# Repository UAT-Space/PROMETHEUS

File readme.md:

# PROMETHEUS

###### If you need to contact me do it [here](mailto:AndrewRLong02@gmail.com). <br> My advice is to entirely remake the build system

### Buildroot
This is the build system for linux that runs on a raspberry pi zero w.  
The python scripts that get data from the hardware are in ./overlay/usr/local/bin/ins.py.  
The script that starts data collection and video recording is at ./overlay/etc/init.d/S91set, the functions of the script has been disabled as data and video were manualy started.  
<br>
The external temperature probe and gps were removed from the scripts because of time constraints.

***DO NOT RE-INIT, YOU WILL LOSE THE KERNEL AND SYSTEM CONFIG. IF THIS HAPPENS YOU WILL HAVE TO REDO ALMOST EVERYTHING.***

### PCBS
The folder "Flight_Comp" contains the custom hat for the raspberry pi zero w.

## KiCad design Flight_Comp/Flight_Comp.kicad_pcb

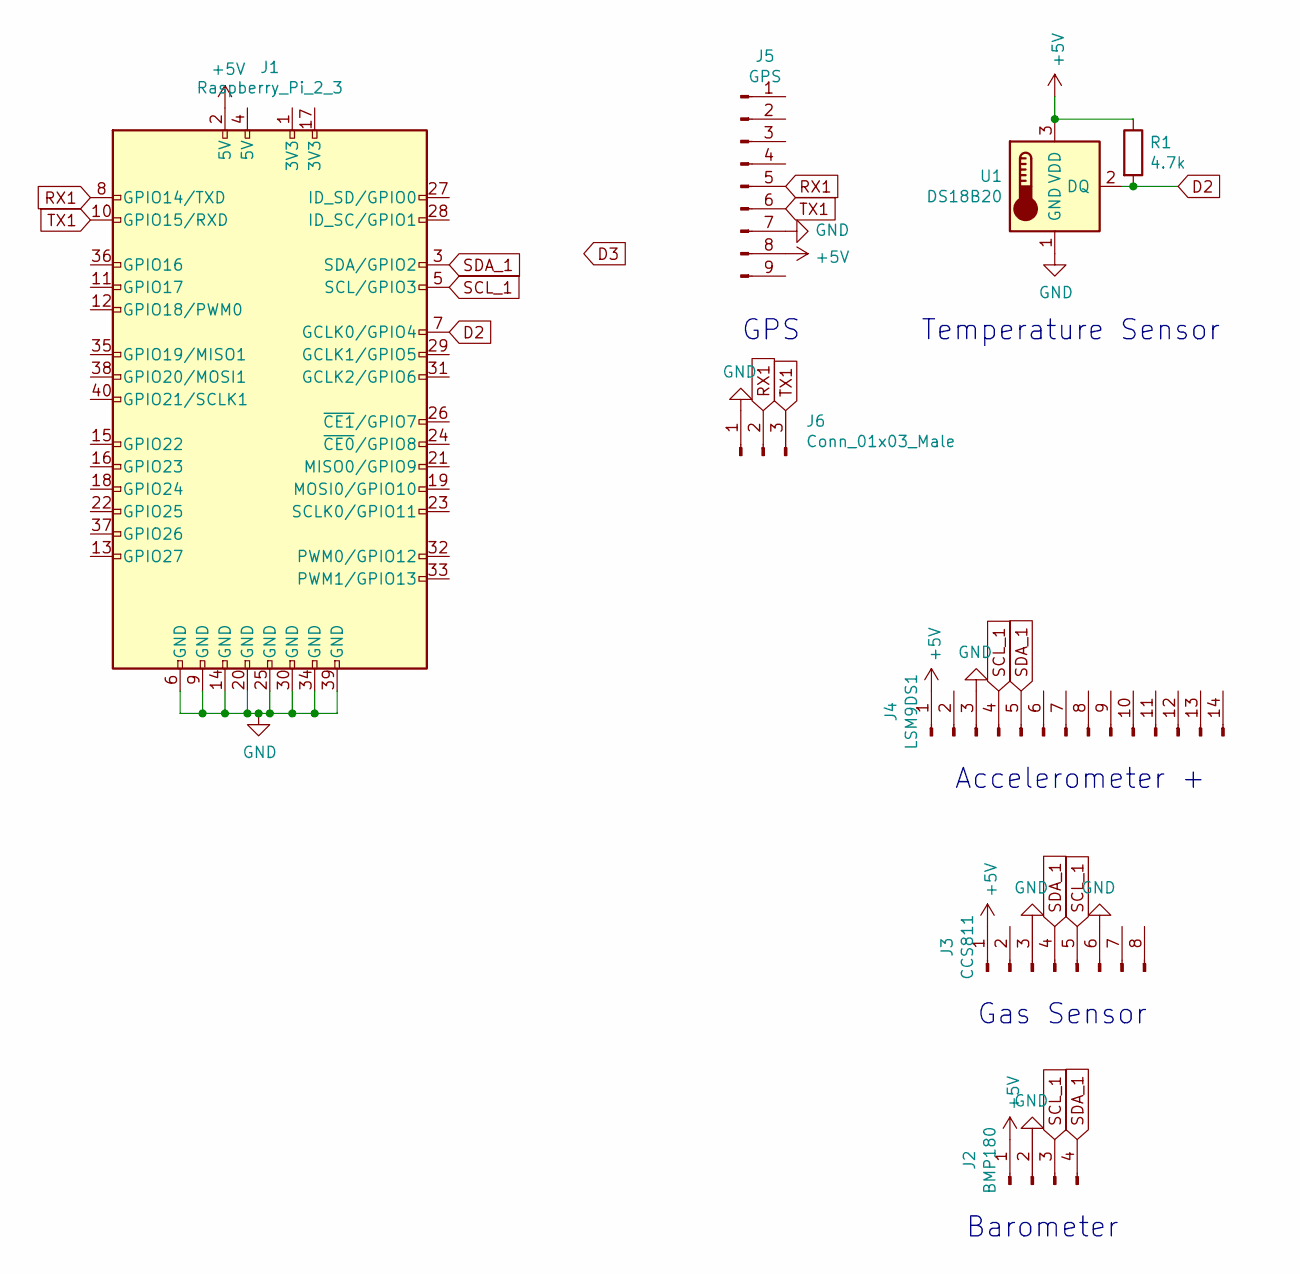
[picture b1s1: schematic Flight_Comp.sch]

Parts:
J1: Raspberry_Pi_2_3; pi zero w
J2: BMP180; JBtec BMP180
J3: CCS811
J4: LSM9DS1
J5: GPS; uGPS Bv3
J6: Conn_01x03_Male; PinSocket_1x03_P2.54mm_Vertical
R1: 4.7k; R_0805_2012Metric
U1: DS18B20; PinSocket_1x03_P2.54mm_Vertical

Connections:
+5V: J1.2 (5V), J2.1, J3.1, J4.1, J5.8, R1.1, U1.3 (VDD)
D2: J1.7 (GCLK0/GPIO4), R1.2, U1.2 (DQ)
GND: J1.6 (GND), J1.9 (GND), J1.14 (GND), J1.20 (GND), J1.25 (GND), J1.30 (GND), J1.34 (GND), J1.39 (GND), J2.2, J3.3, J3.6, J4.3, J5.7, J6.1, U1.1 (GND)
RX1: J1.8 (GPIO14/TXD), J5.5, J6.2
SCL_1: J1.5 (SCL/GPIO3), J2.3, J3.5, J4.4
SDA_1: J1.3 (SDA/GPIO2), J2.4, J3.4, J4.5
TX1: J1.10 (GPIO15/RXD), J5.6, J6.3

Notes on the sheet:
Temperature Sensor
Accelerometer +
Gas Sensor
Barometer
GPS

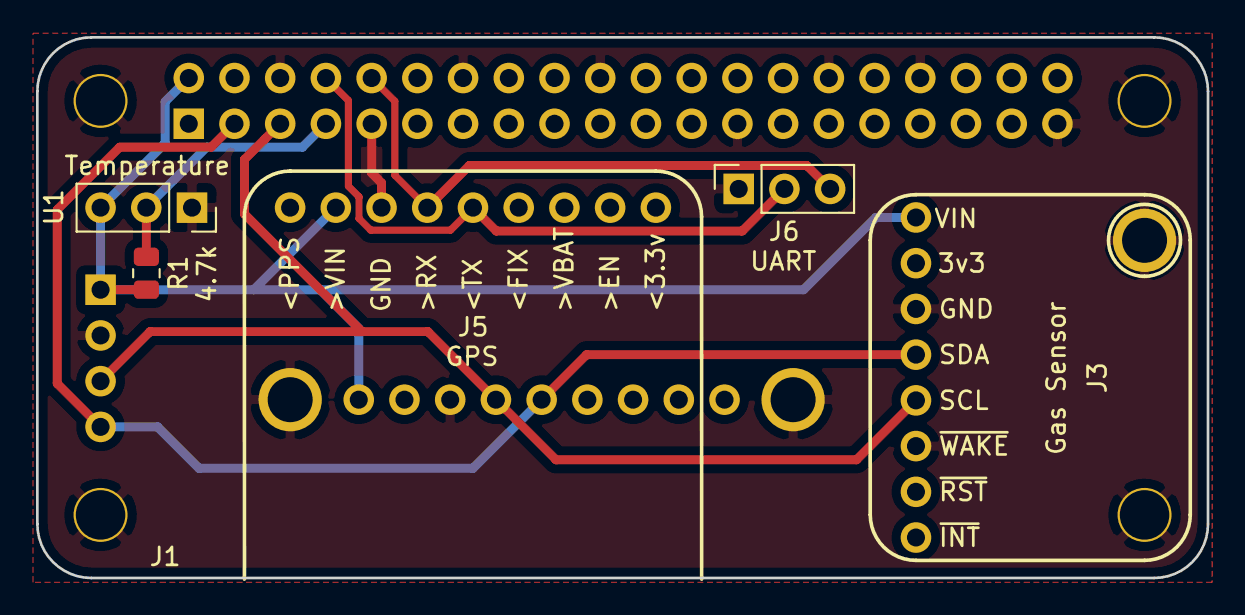
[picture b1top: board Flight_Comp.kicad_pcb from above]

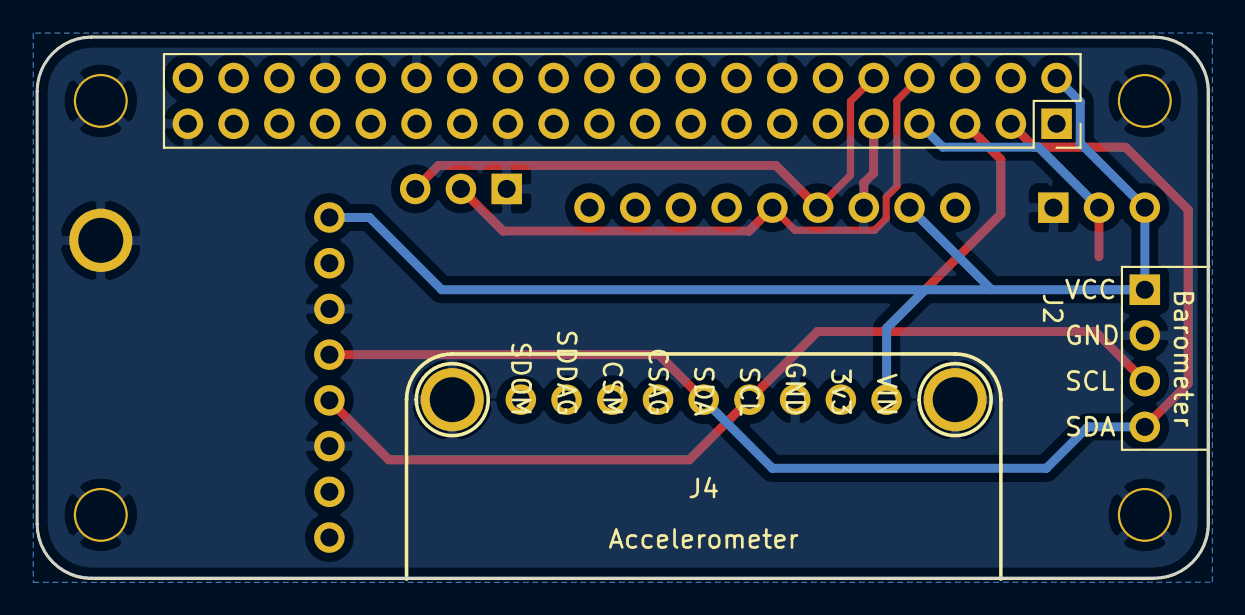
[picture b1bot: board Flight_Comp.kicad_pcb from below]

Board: 2 copper layers, 65.0 x 30.0 mm, 8 parts (2 on the bottom side), 7 nets.

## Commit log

2021-09-09 Inital Commit
